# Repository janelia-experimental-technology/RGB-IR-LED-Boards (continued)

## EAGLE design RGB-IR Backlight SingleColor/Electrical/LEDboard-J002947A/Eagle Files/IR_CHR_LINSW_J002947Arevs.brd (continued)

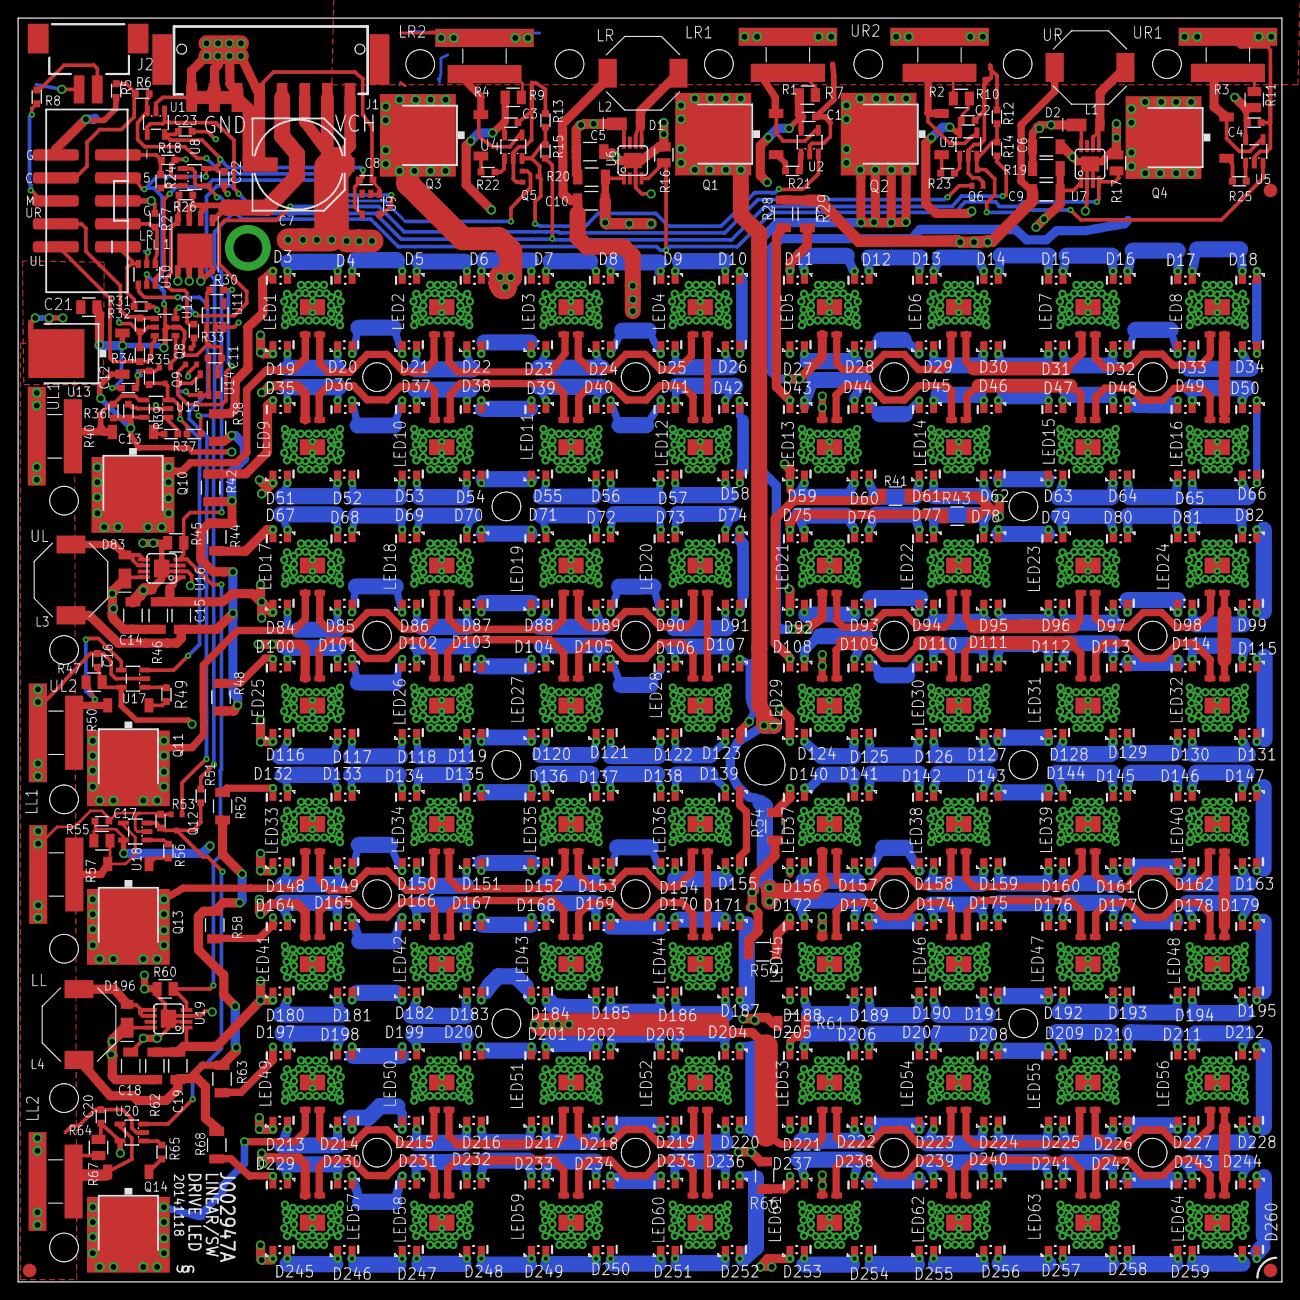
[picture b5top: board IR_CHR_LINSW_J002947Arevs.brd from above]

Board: 4 copper layers, 139.7 x 139.7 mm, 459 parts (0 on the bottom side), 387 nets.

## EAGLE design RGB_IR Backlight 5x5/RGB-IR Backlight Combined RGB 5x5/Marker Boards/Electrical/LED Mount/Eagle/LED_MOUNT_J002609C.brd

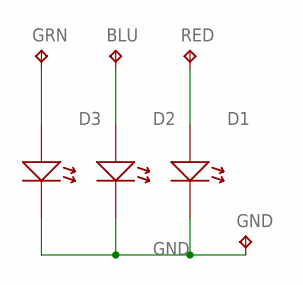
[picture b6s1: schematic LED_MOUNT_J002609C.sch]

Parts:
BLU: TPTP20SQ; TP20SQ
D1, D2, D3: LEDLED_SFH4050; LED_SFH4050
GND: TPTP20SQ; TP20SQ
GRN: TPTP20SQ; TP20SQ
RED: TPTP20SQ; TP20SQ

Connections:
GND: D1.C (K), D2.C (K), D3.C (K), GND.TP
unnamed: BLU.TP, D2.A
unnamed: D1.A, RED.TP
unnamed: D3.A, GRN.TP

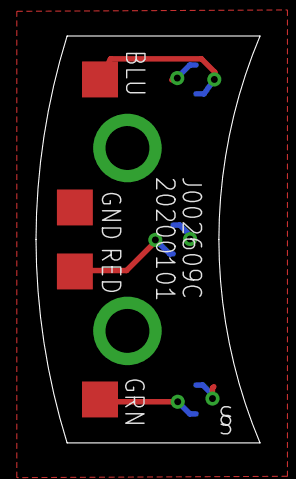
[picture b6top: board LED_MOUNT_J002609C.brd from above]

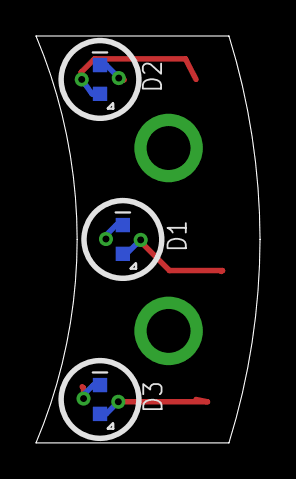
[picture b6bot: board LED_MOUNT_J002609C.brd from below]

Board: 2 copper layers, 12.4 x 22.6 mm, 7 parts (3 on the bottom side), 4 nets.

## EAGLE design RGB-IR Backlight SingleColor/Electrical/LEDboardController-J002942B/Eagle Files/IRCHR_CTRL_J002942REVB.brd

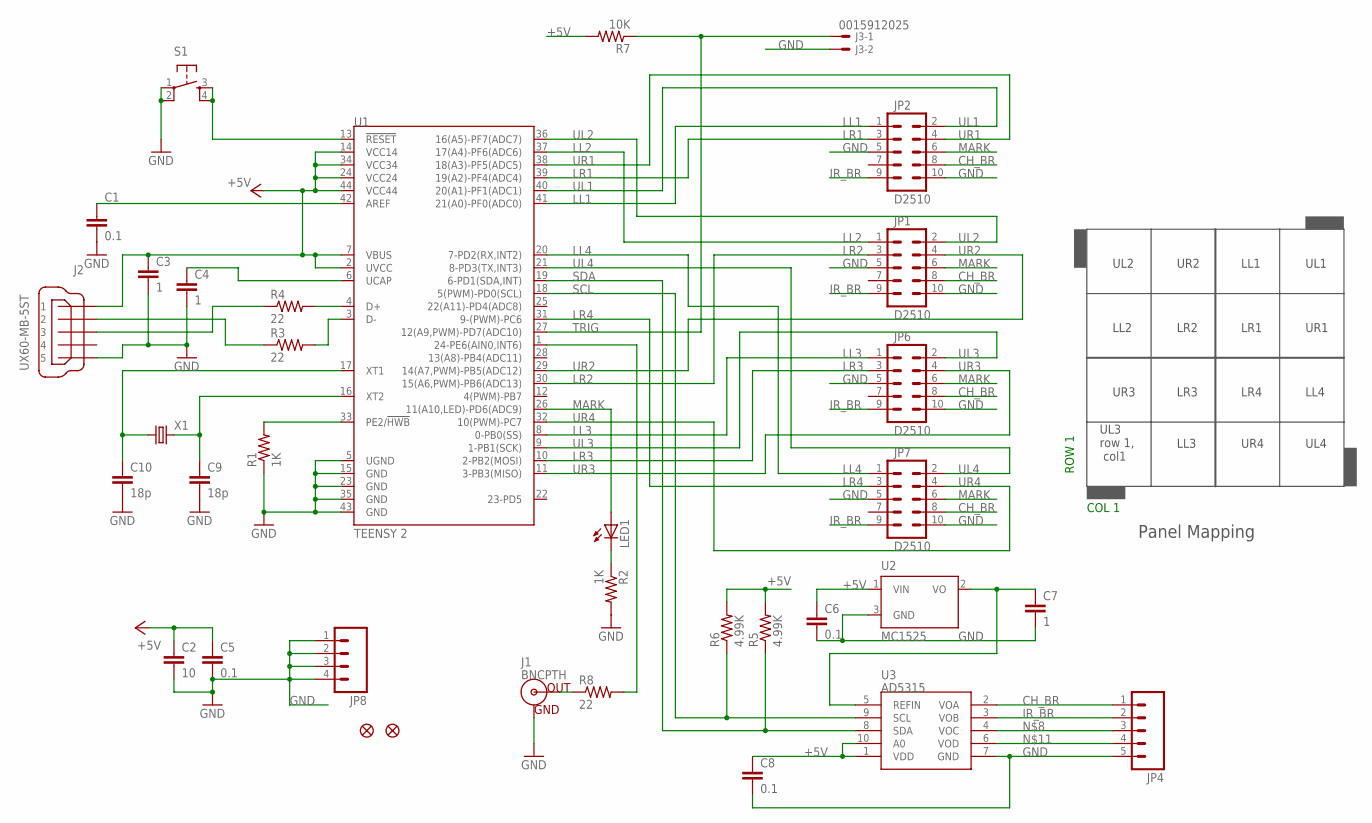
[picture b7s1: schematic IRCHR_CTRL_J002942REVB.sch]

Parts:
C1, C5, C6, C8: 0.1; 0805S
C2: 10; 1206S
C3, C4, C7: 1; 0805S
C9, C10: 18p; 0805S
J1: BNCPTH; BNC
J2: UX60-MB-5ST
J3: 0015912025; 15-91-02
JP1, JP2, JP6, JP7: D2510; 2X5-SHROUDED_SMD_3M
JP3, JP5: FIDUCIAL1X2.5; FIDUCIAL-1X2.5
JP4: M05LOCK; 1X05_LOCK
JP8: M04LOCK; 1X04_LOCK
LED1: LEDCHIP-LED0805; CHIP-LED0805
R1, R2: 1K; 0805S
R3, R4, R8: 22; 0805S
R5, R6: 4.99K; 0805S
R7: 10K; 0805S
S1: TAC_SWITCHSMD; TACTILE_SWITCH_SMD
U1: TEENSY 2; SPARKFUN-DIGITALIC_TQFP44
U2: MC1525; SOT23
U3: AD5315; MSOP10
X1: CRYSTALCTS406; CTS406

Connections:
+5V: C2.1, C3.1, C5.1, C6.1, C8.1, J2.1, R5.2, R6.2, R7.2, U1.2 (UVCC), U1.7 (VBUS), U1.14 (VCC14), U1.24 (VCC24), U1.34 (VCC34), U1.44 (VCC44), U2.1 (VIN), U3.1 (VDD), U3.10 (A0)
CH_BR: JP1.8, JP2.8, JP4.1, JP6.8, JP7.8, U3.2 (VOA)
GND: C1.2, C2.2, C3.2, C4.2, C5.2, C6.2, C7.2, C8.2, C9.2, C10.2, J1.GND, J2.5, J3.2, JP1.5, JP1.10, JP2.5, JP2.10, JP4.5, JP6.5, JP6.10, JP7.5, JP7.10, JP8.1, JP8.2, JP8.3, JP8.4, R1.1, R2.2, S1.1, S1.2, U1.5 (UGND), U1.15 (GND), U1.23 (GND), U1.35 (GND), U1.43 (GND), U2.3 (GND), U3.7 (GND)
IR_BR: JP1.9, JP2.9, JP4.2, JP6.9, JP7.9, U3.3 (VOB)
LL1: JP2.1, U1.41 (21(A0)-PF0(ADC0))
LL2: JP1.1, U1.37 (17(A4)-PF6(ADC6))
LL3: JP6.1, U1.8 (0-PB0(SS))
LL4: JP7.1, U1.20 (7-PD2(RX,INT2))
LR1: JP2.3, U1.39 (19(A2)-PF4(ADC4))
LR2: JP1.3, U1.30 (15(A6,PWM)-PB6(ADC13))
LR3: JP6.3, U1.10 (2-PB2(MOSI))
LR4: JP7.3, U1.31 (9-(PWM)-PC6)
MARK: JP1.6, JP2.6, JP6.6, JP7.6, LED1.A, U1.26 (11(A10,LED)-PD6(ADC9))
unnamed: R3.2, U1.3 (D-)
unnamed: R4.2, U1.4 (D+)
unnamed: S1.3, S1.4, U1.13 (!RESET)
unnamed: JP4.3, U3.4 (VOC)
unnamed: R8.2, U1.1 (24-PE6(AIN0,INT6))
unnamed: J1.S (OUT), R8.1
unnamed: JP4.4, U3.6 (VOD)
unnamed: C7.1, U2.2 (VO), U3.5 (REFIN)
unnamed: C10.1, U1.17 (XT1), X1.1
unnamed: C9.1, U1.16 (XT2), X1.3 (2)
unnamed: R1.2, U1.33 (PE2/!HWB)
unnamed: C1.1, U1.42 (AREF)
unnamed: J2.2, R3.1
unnamed: J2.3, R4.1
unnamed: LED1.C, R2.1
unnamed: C4.1, U1.6 (UCAP)
SCL: R6.1, U1.18 (5(PWM)-PD0(SCL)), U3.9 (SCL)
SDA: R5.1, U1.19 (6-PD1(SDA,INT)), U3.8 (SDA)
TRIG: J3.1, R7.1, U1.27 (12(A9,PWM)-PD7(ADC10))
UL1: JP2.2, U1.40 (20(A1)-PF1(ADC1))
UL2: JP1.2, U1.36 (16(A5)-PF7(ADC7))
UL3: JP6.2, U1.9 (1-PB1(SCK))
UL4: JP7.2, U1.21 (8-PD3(TX,INT3))
UR1: JP2.4, U1.38 (18(A3)-PF5(ADC5))
UR2: JP1.4, U1.29 (14(A7,PWM)-PB5(ADC12))
UR3: JP6.4, U1.11 (3-PB3(MISO))
UR4: JP7.4, U1.32 (10(PWM)-PC7)

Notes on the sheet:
LL1
LR1
UL1
UR1
LL2
UL2
LR2
UR2
LL3
UL3 row 1, col1
LR3
UR3
LL4
LR4
UL4
UR4
ROW 1
COL 1
Panel Mapping

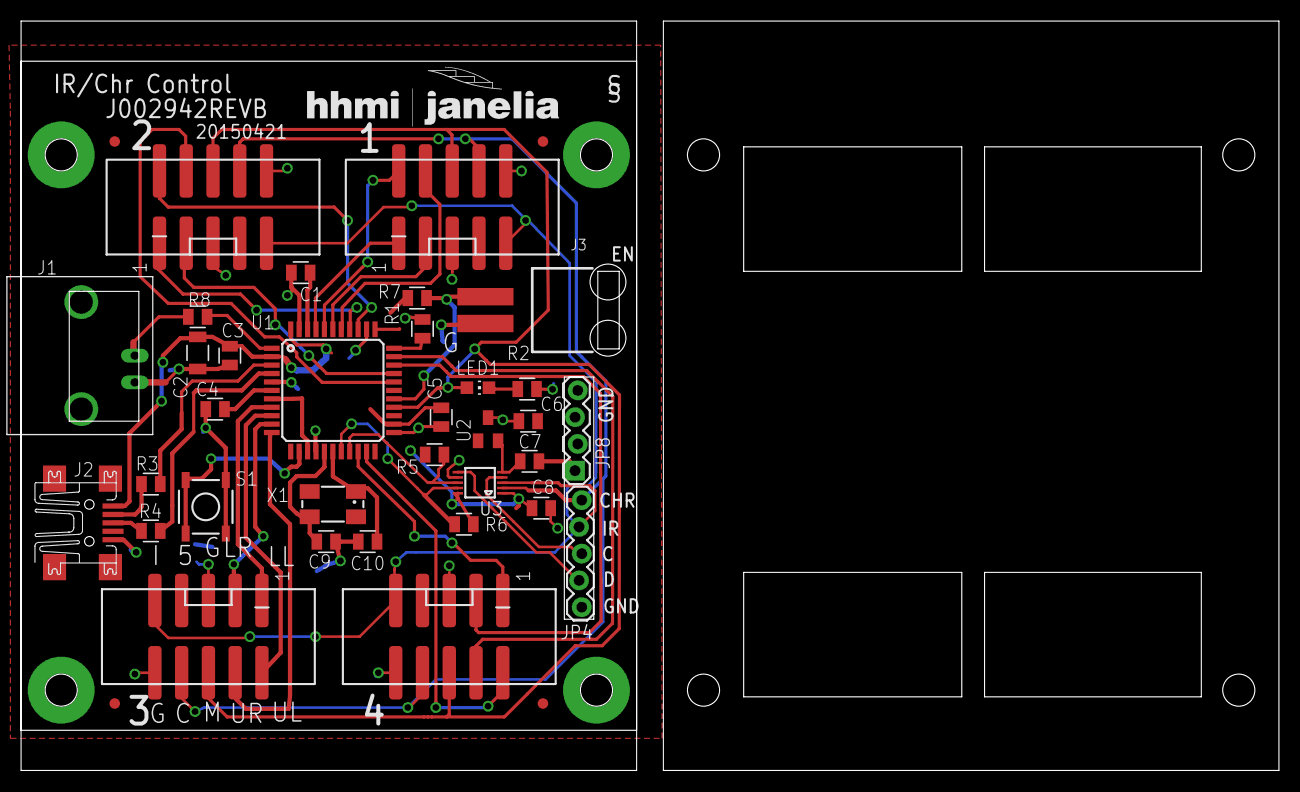
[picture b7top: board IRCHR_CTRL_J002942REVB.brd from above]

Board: 2 copper layers, 119.4 x 71.1 mm, 38 parts (0 on the bottom side), 40 nets.

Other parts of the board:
JP9, JP10: FIDUCIAL1X2.5; FIDUCIAL-1X2.5
U$1: JFRC-LOGOLOGO_JANELIA_2014; LOGO_JANELIA_2014

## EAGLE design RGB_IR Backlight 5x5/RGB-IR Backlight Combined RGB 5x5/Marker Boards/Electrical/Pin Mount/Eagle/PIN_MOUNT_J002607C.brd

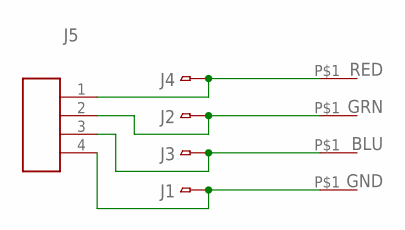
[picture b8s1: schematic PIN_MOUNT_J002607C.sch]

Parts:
BLU: CON10851; 0851_SPRINGPIN
GND: CON10851; 0851_SPRINGPIN
GRN: CON10851; 0851_SPRINGPIN
J1, J2, J3, J4: PADPAD_040; PAD_040
J5: CON4DF13-4-TH; DF13-4-TH
RED: CON10851; 0851_SPRINGPIN

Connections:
unnamed: BLU.P$1, J3.P$1, J5.3
unnamed: GRN.P$1, J2.P$1, J5.2
unnamed: GND.P$1, J1.P$1, J5.4
unnamed: J4.P$1, J5.1, RED.P$1

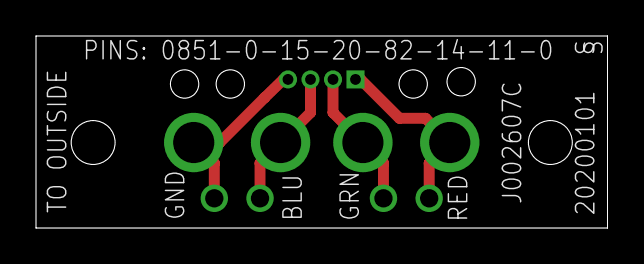
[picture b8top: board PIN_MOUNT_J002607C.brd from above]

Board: 2 copper layers, 31.8 x 10.7 mm, 9 parts (1 on the bottom side), 4 nets.

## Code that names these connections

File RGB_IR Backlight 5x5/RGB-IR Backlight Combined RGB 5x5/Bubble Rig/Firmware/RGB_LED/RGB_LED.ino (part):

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//    C - color channel ('R', 'G', and/or 'B')
 
//#define DEBUG
#define SYNC_PIN_OUT    // if defined, then SYNC pin is set up as camera trigger out,else it is a trigger in
 
// VERSIONS
//
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//    Use pin22 for chip select of IO expander

// 20210127 sws
// - use analogWrite for markers to allow varying intensity, default to constant on, MARKER cmd to change
//    display current Marker Intensity with MARKER cmd

// 20210117 sws
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//   that may cause trouble...

// 20201109 sws
// - add SYNC_PIN_OUT to make sync pin usable as camera trigger out for original RGB board

// 20201029 sws
// - finalize adding in 4 extra chip selects so panel 1 has eight 'quadrants'
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#define IRDAC  8

#define BLUE 0
#define BLU 0
#define GREEN 1
#define GRN 1
#define RED 2
#define IR 3

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#define boardTypePin 23


#define SYNC_ACTIVE_LOW  // marker pin is active low 

//--- pulse states---
#define OFFSTATE 0
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// ====================
// === M A R K E R ====
// ====================
// turn sync pin pin on/off
// a define is used to determine if 'on' is active low

void marker(uint8_t state)
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
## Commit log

2023-11-22 Update README.md
    Add in description of the boards.
2023-12-18 Added Picture and Doc for 7x7, update FW
    FW updated to fix problem with experiment step with 0 pulse width going on forever
2023-12-18 Update RGB_LED.ino
    Put correct version in GitHub
2024-04-17 Correct 5x5 RGB BOM errors and add PCB spec
    Added PCB specs to 5x5 RGB
    Corrected BOM errors on 5x5 RGB
2024-05-08 Added PCB files
2024-05-21 Add 7x7 RGB files
    Add current PCB and cable assembly files for 7x7 RGB panel
2024-05-21 Updated board files
    New Board files for 7x7 RGB, including manufacturing specs for aluminum substrate
2024-06-06 Update RGB_LED.ino
    Change MARKER command from blinking each marker for 1 second to turning markers on and off. So, a MARKER RG will turn on red and green and turn off blue. MARKER with no arguments will turn off all ma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
2024-06-06 Update RGB_LED.ino
    Changed marker (again)
    MARKER color ON to set marker(s) ON
    MARKER color OFF to set marker(s) OFF
    MARKER return on colors
    color: RGBD for red, blue, green, digital
2024-06-24 board change and FW update
    Change Teensy connector to two parts so it can be put into Circuithub
    Fix markerCmd - digital changes weren't changing pin state
2024-09-16 Add license and updated FW
2024-10-15 FW update and Board correction
    P4 should be a SM shrouded male header, not through hole
2024-10-15 Updated Gerber ZIP
2025-01-11 Update BOM and firmware
    Comment out DEBUG define in FW
    Update costing in BOM
    Correct quantities, etc in BOM
2025-01-31 add enumerate cmd, turn on default layers in PCB
2025-07-14 Add LED data sheet and diffuser
2025-07-18 Added rev C files
2025-07-31 fix error in calibration documentation
2025-08-06 redo gain and offset EEPROM access, add INITGO command
2025-08-06 comment out DEBUG
2025-08-06 removed DEBUG from offset/gain inits
2025-08-11 update doc to current MARKER cmd, and in FW, don't add offset and gain to a zero DAC value
2025-09-16 board cleanup, doc cleanup, disable DEBUG in code
2025-10-22 heatsinks, minor code change
2026-02-16 Fix EEPROM not initializing on first boot
2026-02-21 in FW, Fix not loading gain and offsets
2026-03-25 Add Marker Board
2026-05-18 Update RGB_LED.ino
    add ability for markers to follow the intensity setting
